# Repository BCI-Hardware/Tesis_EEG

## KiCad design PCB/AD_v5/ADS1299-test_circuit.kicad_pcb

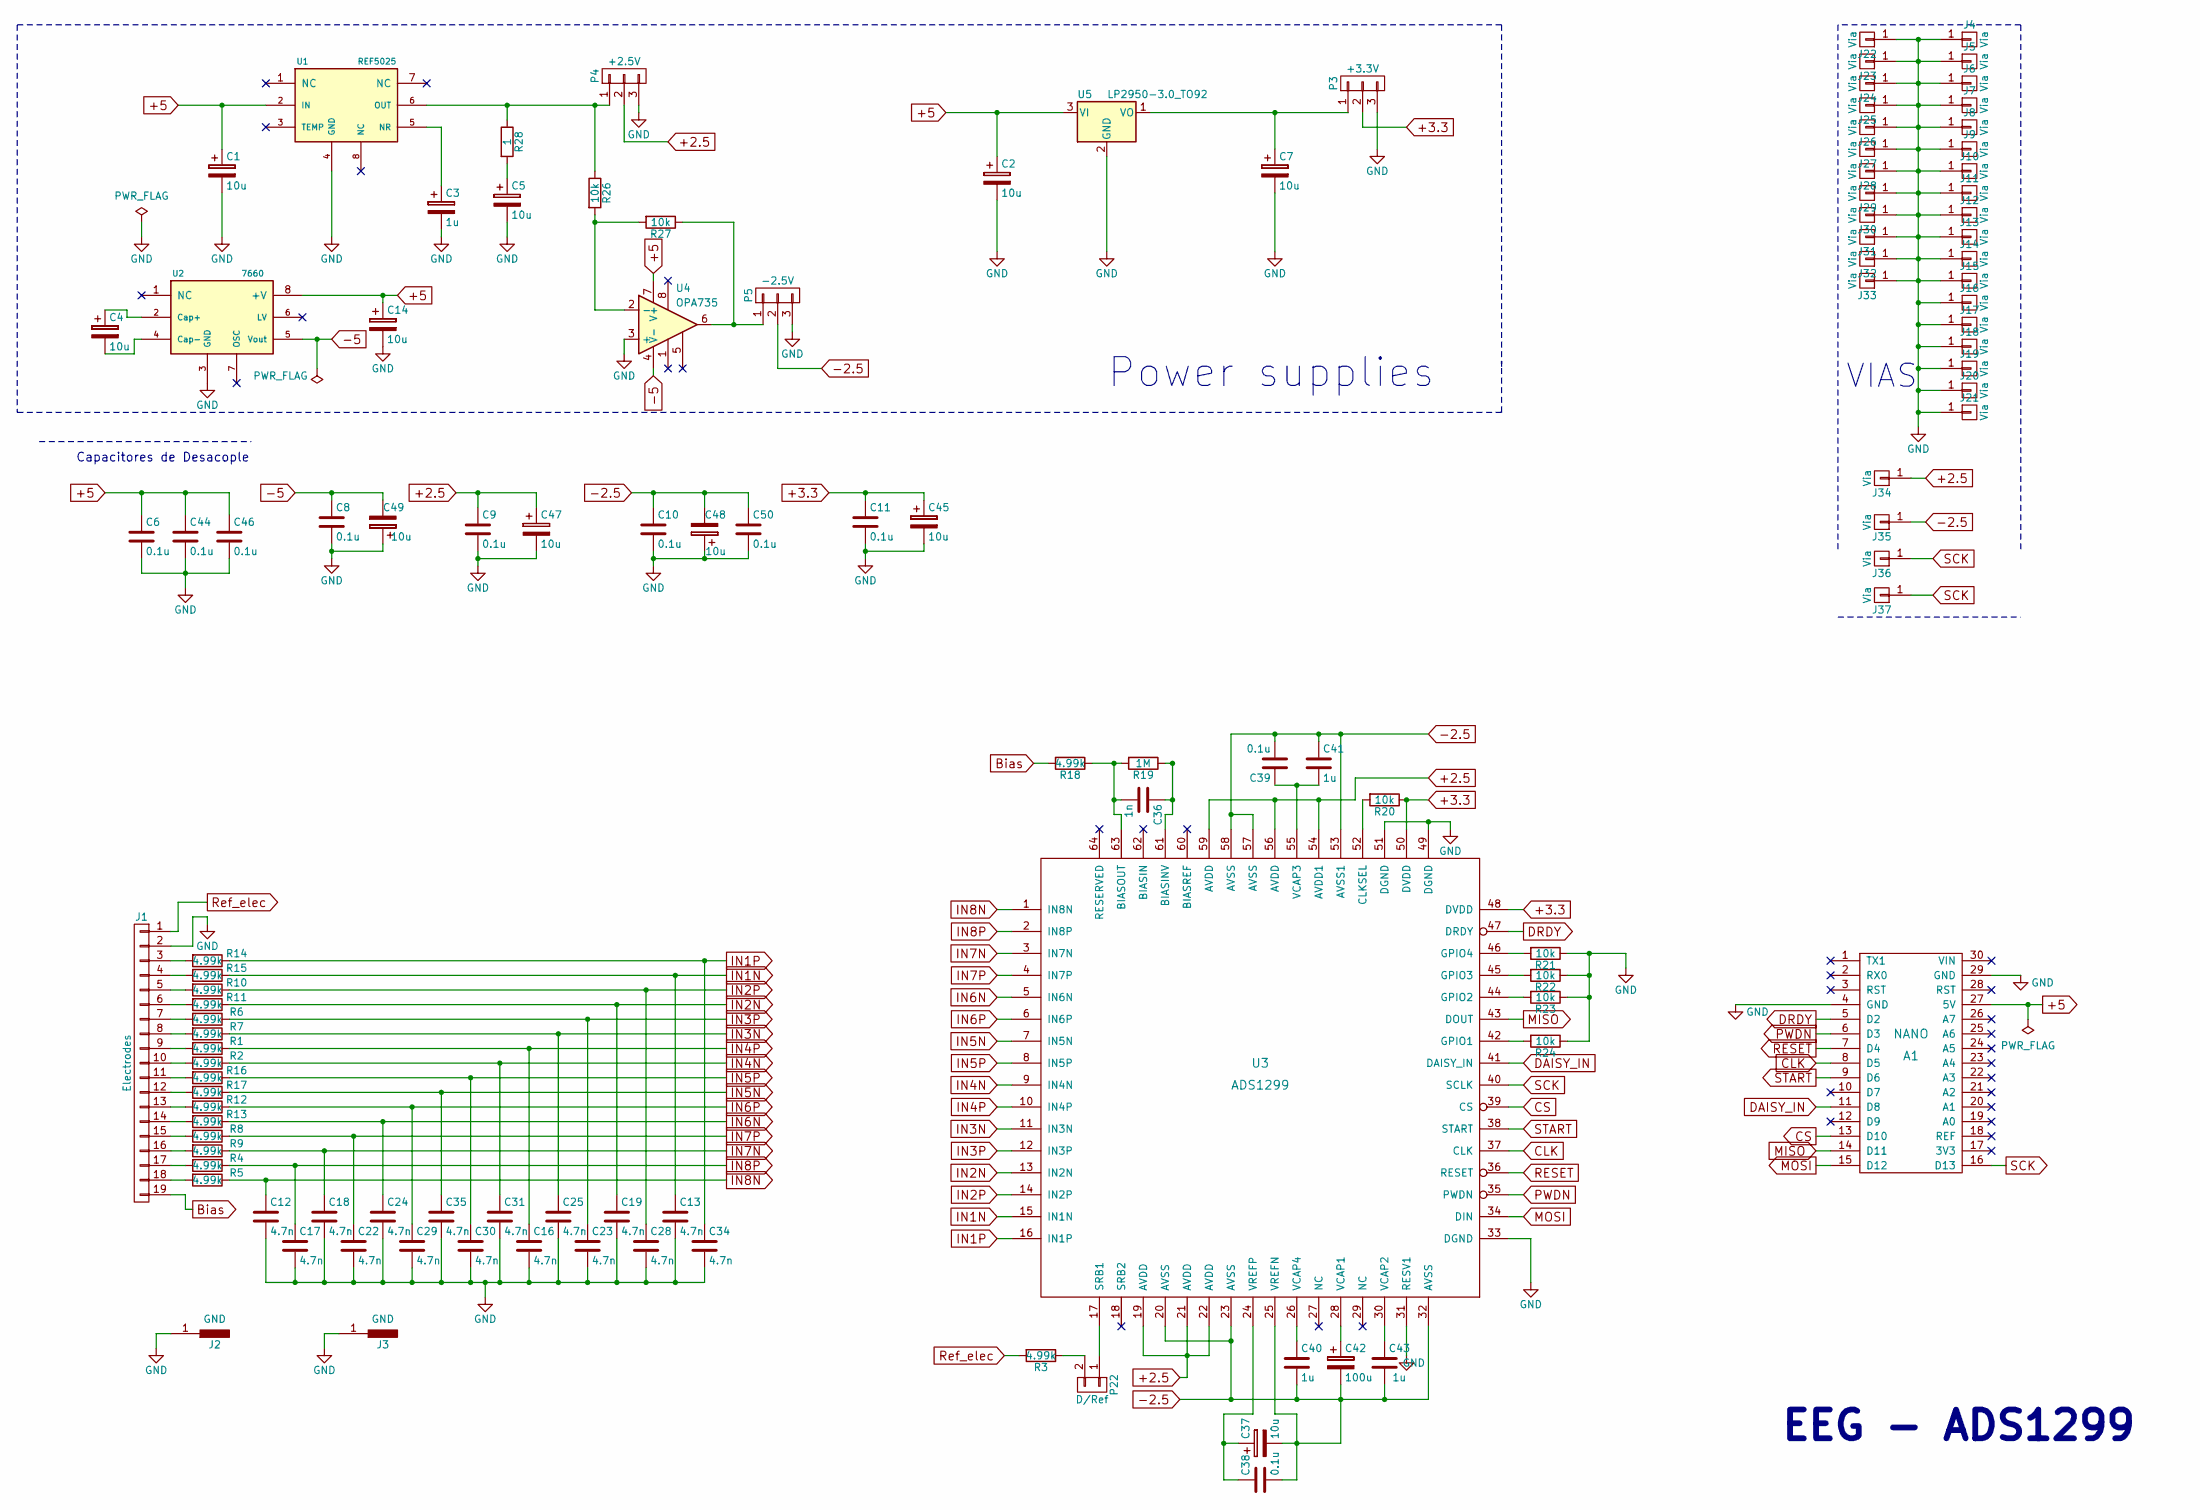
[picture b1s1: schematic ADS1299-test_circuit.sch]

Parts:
A1: NANO
C1, C2, C5, C7, C45, C47, C48, C49: 10u; CP_Elec_6.3x5.8
C3: 1u; CP_Elec_4x4.5
C4, C14: 10u; CP_Radial_D5.0mm_P2.50mm
C6, C8, C9, C10, C11, C38, C39, C44, C46, C50: 0.1u; C_0805
C12, C13, C16, C17, C18, C19, C22, C23, C24, C25, C28, C29, C30, C31, C34, C35: 4.7n; C_0805
C36: 1n; C_0805
C37: 10u; CP_Radial_Tantal_D5.0mm_P2.50mm
C40, C41, C43: 1u; C_0805
C42: 100u; CP_Radial_Tantal_D5.0mm_P2.50mm
J1: Electrodes; Pin_Header_Straight_1x19_Pitch2.54mm
J2, J3: GND; PINtorneado
J4, J5, J6, J7, J8, J9, J10, J11, J12, J13, J14, J15, J16, J17, J18, J19, J20, J21, J22, J23, J24, J25, J26, J27, J28, J29, J30, J31, J32, J33, J34, J35, J36, J37: Via; Pin_Header_Straight_1x01_Pitch2.54mm
P3: +3.3V; Pin_Header_Straight_1x03_Pitch2.54mm
P4: +2.5V; Pin_Header_Straight_1x03_Pitch2.54mm
P5: -2.5V; Pin_Header_Straight_1x03_Pitch2.54mm
P22: D/Ref; Pin_Header_Straight_1x02_Pitch2.54mm
R1, R2, R3, R4, R5, R6, R7, R8, R9, R10, R11, R12, R13, R14, R15, R16, R17, R18: 4.99k; R_0805
R19: 1M; R_0805
R20, R26, R27: 10k; R_0805
R21, R22, R23, R24: 10k; R_1206
R28: 1; R_0805
U1: REF5025; SOIC-8_3.9x4.9mm_Pitch1.27mm
U2: 7660; DIP-8_W7.62mm
U3: ADS1299; LQFP-64_10x10mm_Pitch0.5mm
U4: OPA735; SOIC-8_3.9x4.9mm_Pitch1.27mm
U5: LP2950-3.0_TO92; TO-92_Inline_Wide

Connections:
+2.5: C9.1, C47.1, J34.1, P4.2, U3.19 (AVDD), U3.21 (AVDD), U3.22 (AVDD), U3.54 (AVDD1), U3.56 (AVDD), U3.59 (AVDD)
+3.3: C11.1, C45.1, P3.2, R20.1, U3.48 (DVDD), U3.50 (DVDD)
+5: A1.27 (5V), C1.1, C2.1, C6.1, C14.1, C44.1, C46.1, U1.2 (IN), U2.8 (+V), U4.7 (V+), U5.3 (VI)
-2.5: C10.1, C37.2, C38.2, C39.2, C40.2, C41.1, C42.2, C43.2, C48.2, C50.1, J35.1, P5.2, U3.20 (AVSS), U3.23 (AVSS), U3.25 (VREFN), U3.32 (AVSS), U3.53 (AVSS1), U3.57 (AVSS), U3.58 (AVSS)
-5: C8.1, C49.2, U2.5 (Vout), U4.4 (V-)
Bias: J1.19, R18.2
CLK: A1.8 (D5), U3.37 (CLK)
CS: A1.13 (D10), U3.39 (CS)
DAISY_IN: A1.11 (D8), U3.41 (DAISY_IN)
DRDY: A1.5 (D2), U3.47 (DRDY)
GND: A1.4 (GND), A1.29 (GND), C1.2, C2.2, C3.2, C5.2, C6.2, C7.2, C8.2, C9.2, C10.2, C11.2, C12.2, C13.2, C14.2, C16.2, C17.2, C18.2, C19.2, C22.2, C23.2, C24.2, C25.2, C28.2, C29.2, C30.2, C31.2, C34.2, C35.2, C44.2, C45.2, C46.2, C47.2, C48.1, C49.1, C50.2, J1.2, J2.1, J3.1, J4.1, J5.1, J6.1, J7.1, J8.1, J9.1, J10.1, J11.1, J12.1, J13.1, J14.1, J15.1, J16.1, J17.1, J18.1, J19.1, J20.1, J21.1, J22.1, J23.1, J24.1, J25.1, J26.1, J27.1, J28.1, J29.1, J30.1, J31.1, J32.1, J33.1, P3.3, P4.3, P5.3, R21.1, R22.1, R23.1, R24.1, U1.4 (GND), U2.3 (GND), U3.31 (RESV1), U3.33 (DGND), U3.49 (DGND), U3.51 (DGND), U4.3 (+), U5.2 (GND)
IN1N: C13.1, R15.1, U3.15 (IN1N)
IN1P: C34.1, R14.1, U3.16 (IN1P)
IN2N: C19.1, R11.1, U3.13 (IN2N)
IN2P: C28.1, R10.1, U3.14 (IN2P)
IN3N: C25.1, R7.1, U3.11 (IN3N)
IN3P: C23.1, R6.1, U3.12 (IN3P)
IN4N: C31.1, R2.1, U3.9 (IN4N)
IN4P: C16.1, R1.1, U3.10 (IN4P)
IN5N: C35.1, R17.1, U3.7 (IN5N)
IN5P: C30.1, R16.1, U3.8 (IN5P)
IN6N: C24.1, R13.1, U3.5 (IN6N)
IN6P: C29.1, R12.1, U3.6 (IN6P)
IN7N: C18.1, R9.1, U3.3 (IN7N)
IN7P: C22.1, R8.1, U3.4 (IN7P)
IN8N: C12.1, R5.1, U3.1 (IN8N)
IN8P: C17.1, R4.1, U3.2 (IN8P)
MISO: A1.14 (D11), U3.43 (DOUT)
MOSI: A1.15 (D12), U3.34 (DIN)
unnamed: C3.1, U1.5 (NR)
unnamed: C4.1, U2.2 (Cap+)
unnamed: C4.2, U2.4 (Cap-)
unnamed: C5.1, R28.2
unnamed: C7.1, P3.1, U5.1 (VO)
unnamed: C36.1, R19.1, U3.61 (BIASINV)
unnamed: C36.2, R18.1, R19.2, U3.63 (BIASOUT)
unnamed: C37.1, C38.1, U3.24 (VREFP)
unnamed: C39.1, C41.2, U3.55 (VCAP3)
unnamed: C40.1, U3.26 (VCAP4)
unnamed: C42.1, U3.28 (VCAP1)
unnamed: C43.1, U3.30 (VCAP2)
unnamed: J1.3, R14.2
unnamed: J1.4, R15.2
unnamed: J1.5, R10.2
unnamed: J1.6, R11.2
unnamed: J1.7, R6.2
unnamed: J1.8, R7.2
unnamed: J1.9, R1.2
unnamed: J1.10, R2.2
unnamed: J1.11, R16.2
unnamed: J1.12, R17.2
unnamed: J1.13, R12.2
unnamed: J1.14, R13.2
unnamed: J1.15, R8.2
unnamed: J1.16, R9.2
unnamed: J1.17, R4.2
unnamed: J1.18, R5.2
unnamed: P4.1, R26.1, R28.1, U1.6 (OUT)
unnamed: P5.1, R27.1, U4.6
unnamed: P22.1, U3.17 (SRB1)
unnamed: P22.2, R3.1
unnamed: R20.2, U3.52 (CLKSEL)
unnamed: R21.2, U3.46 (GPIO4)
unnamed: R22.2, U3.45 (GPIO3)
unnamed: R23.2, U3.44 (GPIO2)
unnamed: R24.2, U3.42 (GPIO1)
unnamed: R26.2, R27.2, U4.2 (-)
PWDN: A1.6 (D3), U3.35 (PWDN)
RESET: A1.7 (D4), U3.36 (RESET)
Ref_elec: J1.1, R3.2
SCK: A1.16 (D13), J36.1, J37.1, U3.40 (SCLK)
START: A1.9 (D6), U3.38 (START)

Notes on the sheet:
Power supplies
Capacitores de Desacople
EEG - ADS1299
VIAS

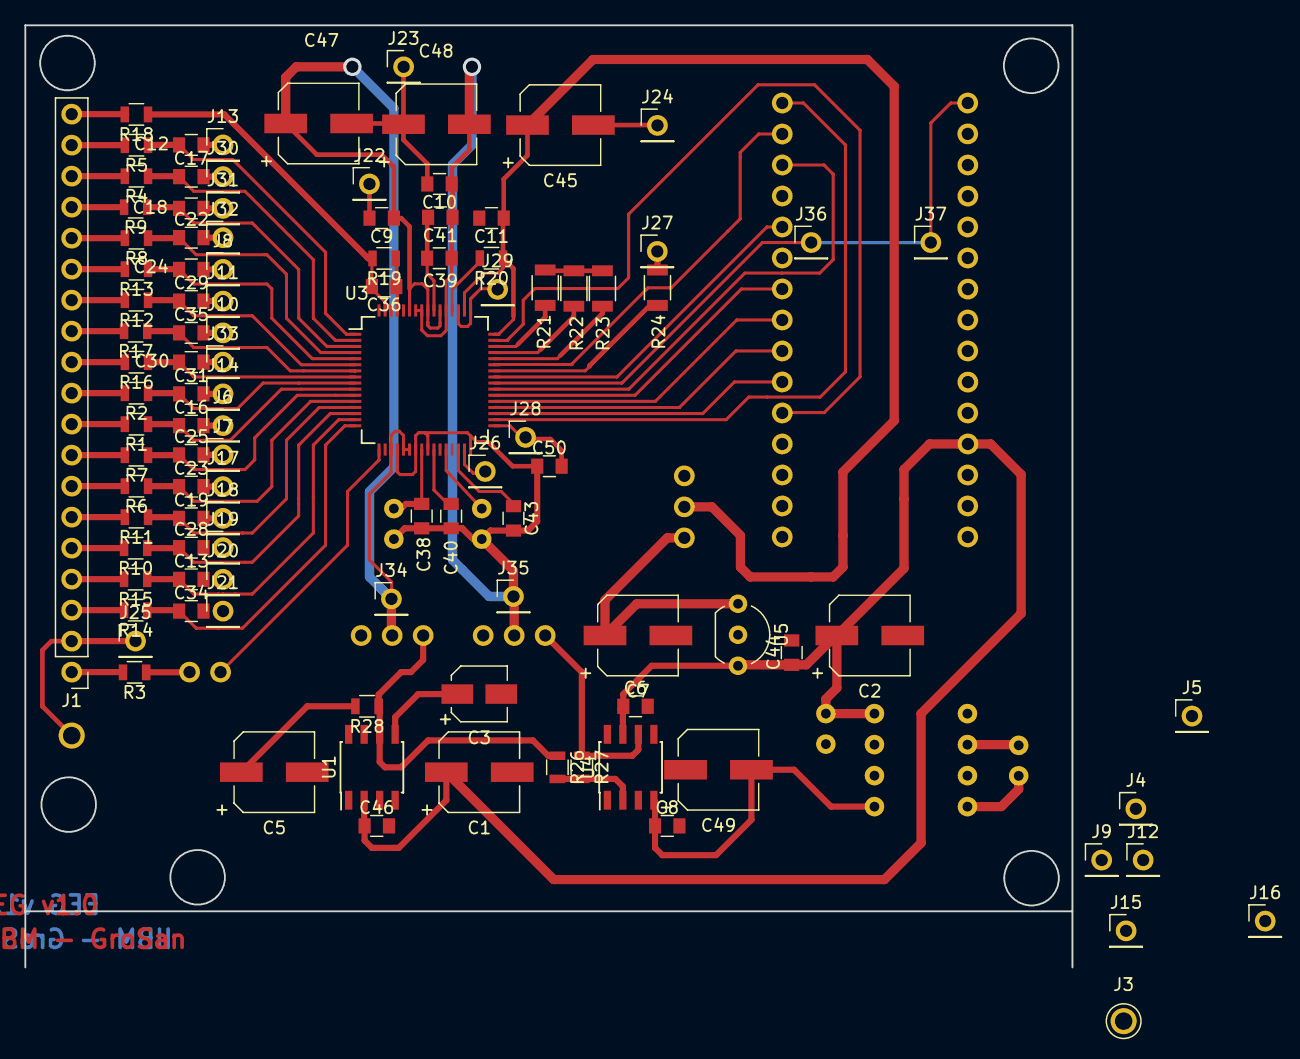
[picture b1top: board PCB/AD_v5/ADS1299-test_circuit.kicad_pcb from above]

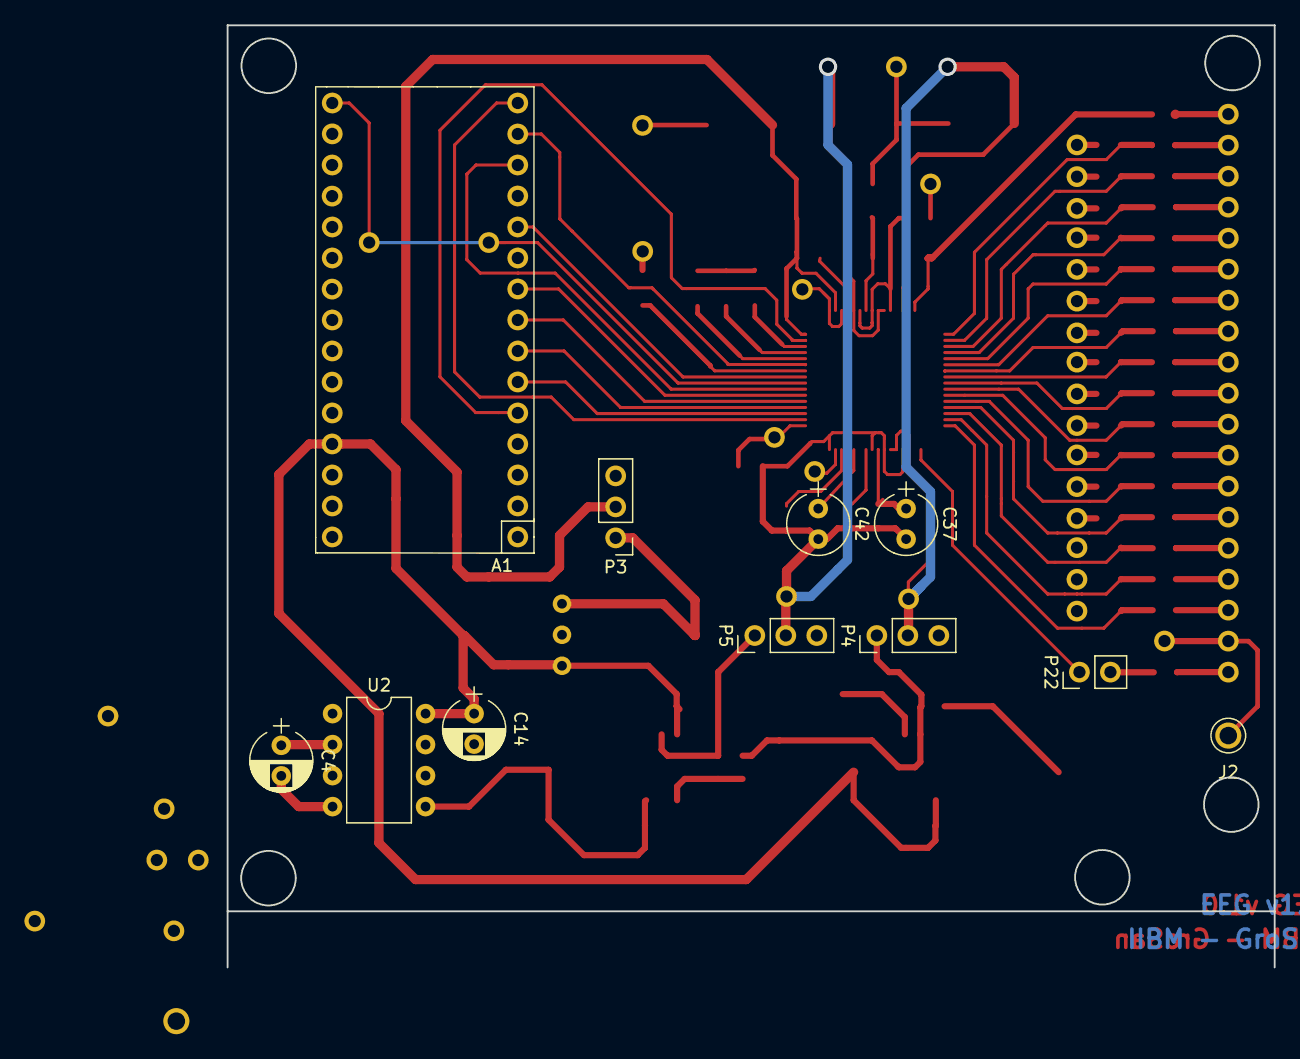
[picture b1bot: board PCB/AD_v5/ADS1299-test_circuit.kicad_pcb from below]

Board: 2 copper layers, 85.8 x 77.2 mm, 117 parts (11 on the bottom side), 72 nets.

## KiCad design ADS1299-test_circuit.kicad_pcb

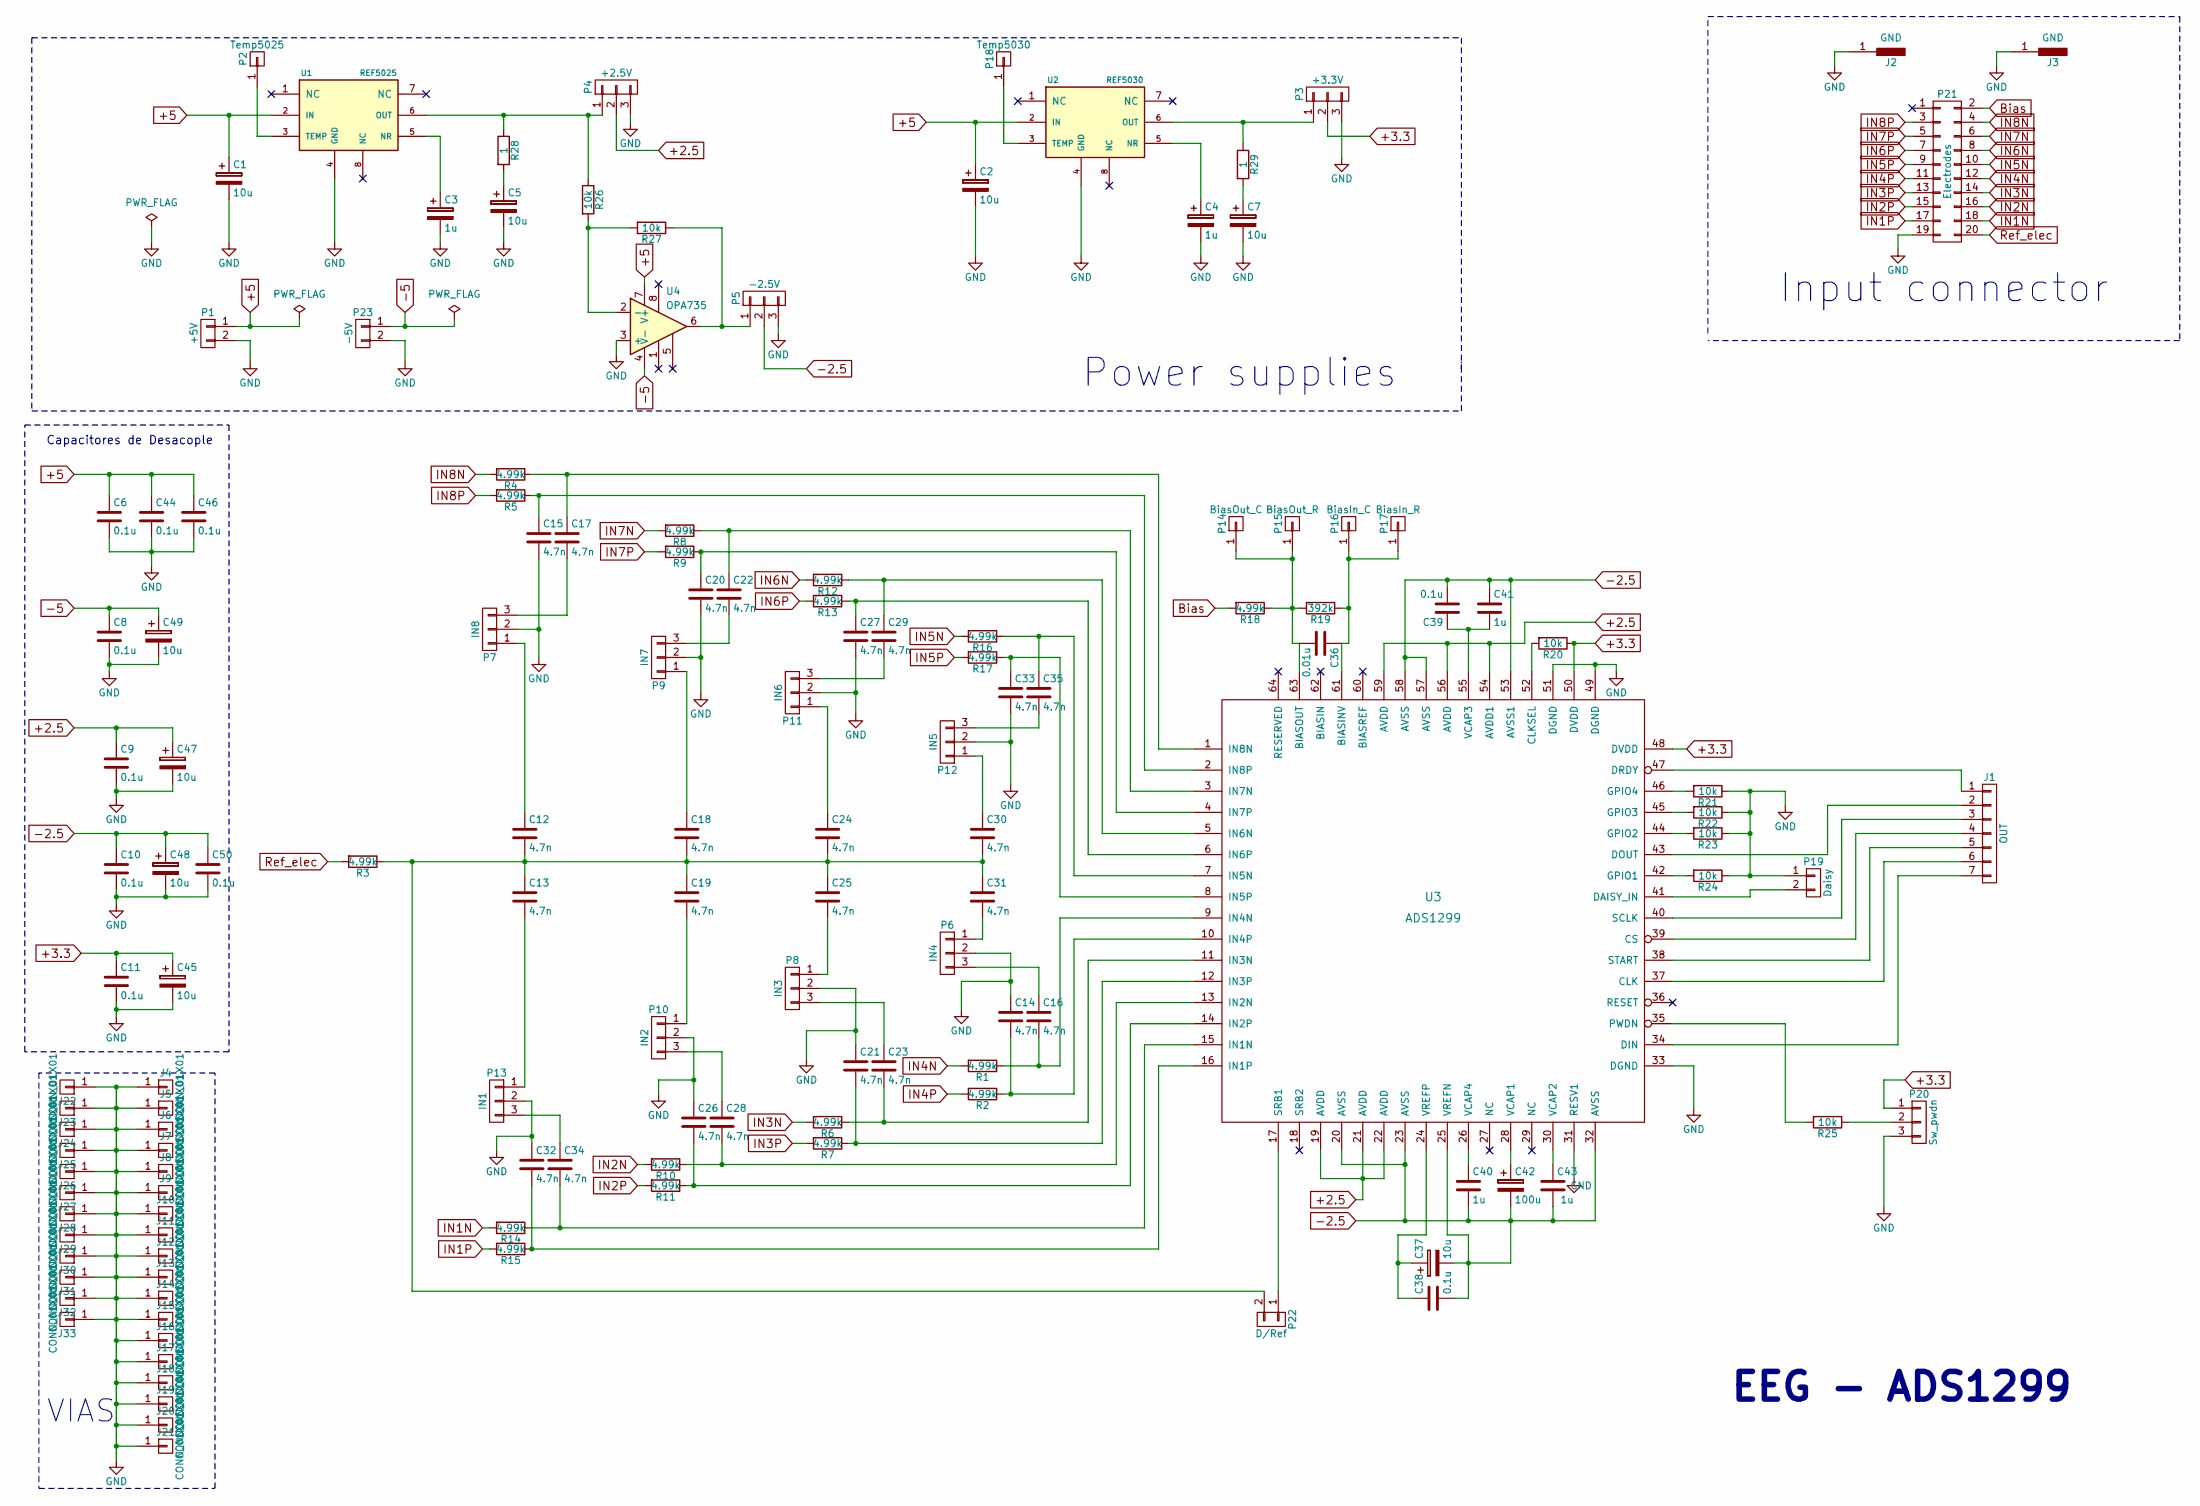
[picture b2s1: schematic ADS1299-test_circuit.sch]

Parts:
C1, C2, C5, C7, C45, C47, C48, C49: 10u; CP_Elec_6.3x5.8
C3, C4: 1u; CP_Elec_4x4.5
C6, C8, C9, C10, C11, C38, C39, C44, C46, C50: 0.1u; C_0805
C12, C13, C18, C19, C24, C25, C30, C31: 4.7n; C_0805
C14, C15, C16, C17, C20, C21, C22, C23, C26, C27, C28, C29, C32, C33, C34, C35: 4.7n; C_1206
C36: 0.01u; C_0805
C37: 10u; CP_Radial_Tantal_D5.0mm_P2.50mm
C40, C41, C43: 1u; C_0805
C42: 100u; CP_Radial_Tantal_D5.0mm_P2.50mm
J1: OUT; Pin_Header_Straight_1x07_Pitch2.54mm
J2, J3: GND; PINtorneado
J4, J5, J6, J7, J8, J9, J10, J11, J12, J13, J14, J15, J16, J17, J18, J19, J20, J21, J22, J23, J24, J25, J26, J27, J28, J29, J30, J31, J32, J33: CONN_01X01; Pin_Header_Straight_1x01_Pitch2.54mm
P1: +5V; Pin_Header_Straight_1x02_Pitch2.54mm
P2: Temp5025; Pin_Header_Straight_1x01_Pitch2.54mm
P3: +3.3V; Pin_Header_Straight_1x03_Pitch2.54mm
P4: +2.5V; Pin_Header_Straight_1x03_Pitch2.54mm
P5: -2.5V; Pin_Header_Straight_1x03_Pitch2.54mm
P6: IN4; Pin_Header_Straight_1x03_Pitch2.54mm
P7: IN8; Pin_Header_Straight_1x03_Pitch2.54mm
P8: IN3; Pin_Header_Straight_1x03_Pitch2.54mm
P9: IN7; Pin_Header_Straight_1x03_Pitch2.54mm
P10: IN2; Pin_Header_Straight_1x03_Pitch2.54mm
P11: IN6; Pin_Header_Straight_1x03_Pitch2.54mm
P12: IN5; Pin_Header_Straight_1x03_Pitch2.54mm
P13: IN1; Pin_Header_Straight_1x03_Pitch2.54mm
P14: BiasOut_C; Pin_Header_Straight_1x01_Pitch2.54mm
P15: BiasOut_R; Pin_Header_Straight_1x01_Pitch2.54mm
P16: BiasIn_C; Pin_Header_Straight_1x01_Pitch2.54mm
P17: BiasIn_R; Pin_Header_Straight_1x01_Pitch2.54mm
P18: Temp5030; Pin_Header_Straight_1x01_Pitch2.54mm
P19: Daisy; Pin_Header_Straight_1x02_Pitch2.54mm
P20: Sw_pwdn; Pin_Header_Straight_1x03_Pitch2.54mm
P21: Electrodes; Pin_Header_Straight_2x10_Pitch2.54mm
P22: D/Ref; Pin_Header_Straight_1x02_Pitch2.54mm
P23: -5V; Pin_Header_Straight_1x02_Pitch2.54mm
R1, R2, R3, R4, R5, R6, R7, R8, R9, R10, R11, R12, R13, R14, R15, R16, R17, R18: 4.99k; R_0805
R19: 392k; R_0805
R20, R26, R27: 10k; R_0805
R21, R22, R23, R24, R25: 10k; R_1206
R28, R29: 1; R_0805
U1: REF5025; SOIC-8_3.9x4.9mm_Pitch1.27mm
U2: REF5030; SOIC-8_3.9x4.9mm_Pitch1.27mm
U3: ADS1299; LQFP-64_10x10mm_Pitch0.5mm
U4: OPA735; SOIC-8_3.9x4.9mm_Pitch1.27mm

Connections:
+2.5: C9.1, C47.1, P4.2, U3.19 (AVDD), U3.21 (AVDD), U3.22 (AVDD), U3.54 (AVDD1), U3.56 (AVDD), U3.59 (AVDD)
+3.3: C11.1, C45.1, P3.2, P20.1, R20.1, U3.48 (DVDD), U3.50 (DVDD)
+5: C1.1, C2.1, C6.1, C44.1, C46.1, P1.1, U1.2 (IN), U2.2 (IN), U4.7 (V+)
-2.5: C10.1, C37.2, C38.2, C39.2, C40.2, C41.1, C42.2, C43.2, C48.1, C50.1, P5.2, U3.20 (AVSS), U3.23 (AVSS), U3.25 (VREFN), U3.32 (AVSS), U3.53 (AVSS1), U3.57 (AVSS), U3.58 (AVSS)
-5: C8.1, C49.1, P23.1, U4.4 (V-)
Bias: P21.2, R18.2
GND: C1.2, C2.2, C3.2, C4.2, C5.2, C6.2, C7.2, C8.2, C9.2, C10.2, C11.2, C14.1, C15.2, C20.2, C21.1, C26.1, C27.2, C32.1, C33.2, C44.2, C45.2, C46.2, C47.2, C48.2, C49.2, C50.2, J2.1, J3.1, J4.1, J5.1, J6.1, J7.1, J8.1, J9.1, J10.1, J11.1, J12.1, J13.1, J14.1, J15.1, J16.1, J17.1, J18.1, J19.1, J20.1, J21.1, J22.1, J23.1, J24.1, J25.1, J26.1, J27.1, J28.1, J29.1, J30.1, J31.1, J32.1, J33.1, P1.2, P3.3, P4.3, P5.3, P6.2, P7.2, P8.2, P9.2, P10.2, P11.2, P12.2, P13.2, P19.1, P20.3, P21.19, P23.2, R21.1, R22.1, R23.1, R24.1, U1.4 (GND), U2.4 (GND), U3.31 (RESV1), U3.33 (DGND), U3.49 (DGND), U3.51 (DGND), U4.3 (+)
IN1N: P21.18, R14.2
IN1P: P21.17, R15.2
IN2N: P21.16, R10.2
IN2P: P21.15, R11.2
IN3N: P21.14, R6.2
IN3P: P21.13, R7.2
IN4N: P21.12, R1.2
IN4P: P21.11, R2.2
IN5N: P21.10, R16.2
IN5P: P21.9, R17.2
IN6N: P21.8, R12.2
IN6P: P21.7, R13.2
IN7N: P21.6, R8.2
IN7P: P21.5, R9.2
IN8N: P21.4, R4.2
IN8P: P21.3, R5.2
unnamed: C3.1, U1.5 (NR)
unnamed: C4.1, U2.5 (NR)
unnamed: C5.1, R28.2
unnamed: C7.1, R29.2
unnamed: C12.1, P7.1
unnamed: C12.2, C13.1, C18.2, C19.1, C24.2, C25.1, C30.2, C31.1, P22.2, R3.1
unnamed: C13.2, P13.1
unnamed: C14.2, R2.1, U3.10 (IN4P)
unnamed: C15.1, R5.1, U3.2 (IN8P)
unnamed: C16.1, P6.3
unnamed: C16.2, R1.1, U3.9 (IN4N)
unnamed: C17.1, R4.1, U3.1 (IN8N)
unnamed: C17.2, P7.3
unnamed: C18.1, P9.1
unnamed: C19.2, P10.1
unnamed: C20.1, R9.1, U3.4 (IN7P)
unnamed: C21.2, R7.1, U3.12 (IN3P)
unnamed: C22.1, R8.1, U3.3 (IN7N)
unnamed: C22.2, P9.3
unnamed: C23.1, P8.3
unnamed: C23.2, R6.1, U3.11 (IN3N)
unnamed: C24.1, P11.1
unnamed: C25.2, P8.1
unnamed: C26.2, R11.1, U3.14 (IN2P)
unnamed: C27.1, R13.1, U3.6 (IN6P)
unnamed: C28.1, P10.3
unnamed: C28.2, R10.1, U3.13 (IN2N)
unnamed: C29.1, R12.1, U3.5 (IN6N)
unnamed: C29.2, P11.3
unnamed: C30.1, P12.1
unnamed: C31.2, P6.1
unnamed: C32.2, R15.1, U3.16 (IN1P)
unnamed: C33.1, R17.1, U3.8 (IN5P)
unnamed: C34.1, P13.3
unnamed: C34.2, R14.1, U3.15 (IN1N)
unnamed: C35.1, R16.1, U3.7 (IN5N)
unnamed: C35.2, P12.3
unnamed: C36.1, P16.1, P17.1, R19.1, U3.61 (BIASINV)
unnamed: C36.2, P14.1, P15.1, R18.1, R19.2, U3.63 (BIASOUT)
unnamed: C37.1, C38.1, U3.24 (VREFP)
unnamed: C39.1, C41.2, U3.55 (VCAP3)
unnamed: C40.1, U3.26 (VCAP4)
unnamed: C42.1, U3.28 (VCAP1)
unnamed: C43.1, U3.30 (VCAP2)
unnamed: J1.1, U3.47 (DRDY)
unnamed: J1.2, U3.43 (DOUT)
unnamed: J1.3, U3.40 (SCLK)
unnamed: J1.4, U3.39 (CS)
unnamed: J1.5, U3.38 (START)
unnamed: J1.6, U3.37 (CLK)
unnamed: J1.7, U3.34 (DIN)
unnamed: P2.1, U1.3 (TEMP)
unnamed: P3.1, R29.1, U2.6 (OUT)
unnamed: P4.1, R26.1, R28.1, U1.6 (OUT)
unnamed: P5.1, R27.1, U4.6
unnamed: P18.1, U2.3 (TEMP)
unnamed: P19.2, U3.41 (DAISY_IN)
unnamed: P20.2, R25.1
unnamed: P22.1, U3.17 (SRB1)
unnamed: R20.2, U3.52 (CLKSEL)
unnamed: R21.2, U3.46 (GPIO4)
unnamed: R22.2, U3.45 (GPIO3)
unnamed: R23.2, U3.44 (GPIO2)
unnamed: R24.2, U3.42 (GPIO1)
unnamed: R25.2, U3.35 (PWDN)
unnamed: R26.2, R27.2, U4.2 (-)
Ref_elec: P21.20, R3.2

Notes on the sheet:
Power supplies
Input connector
Capacitores de Desacople
EEG - ADS1299
VIAS

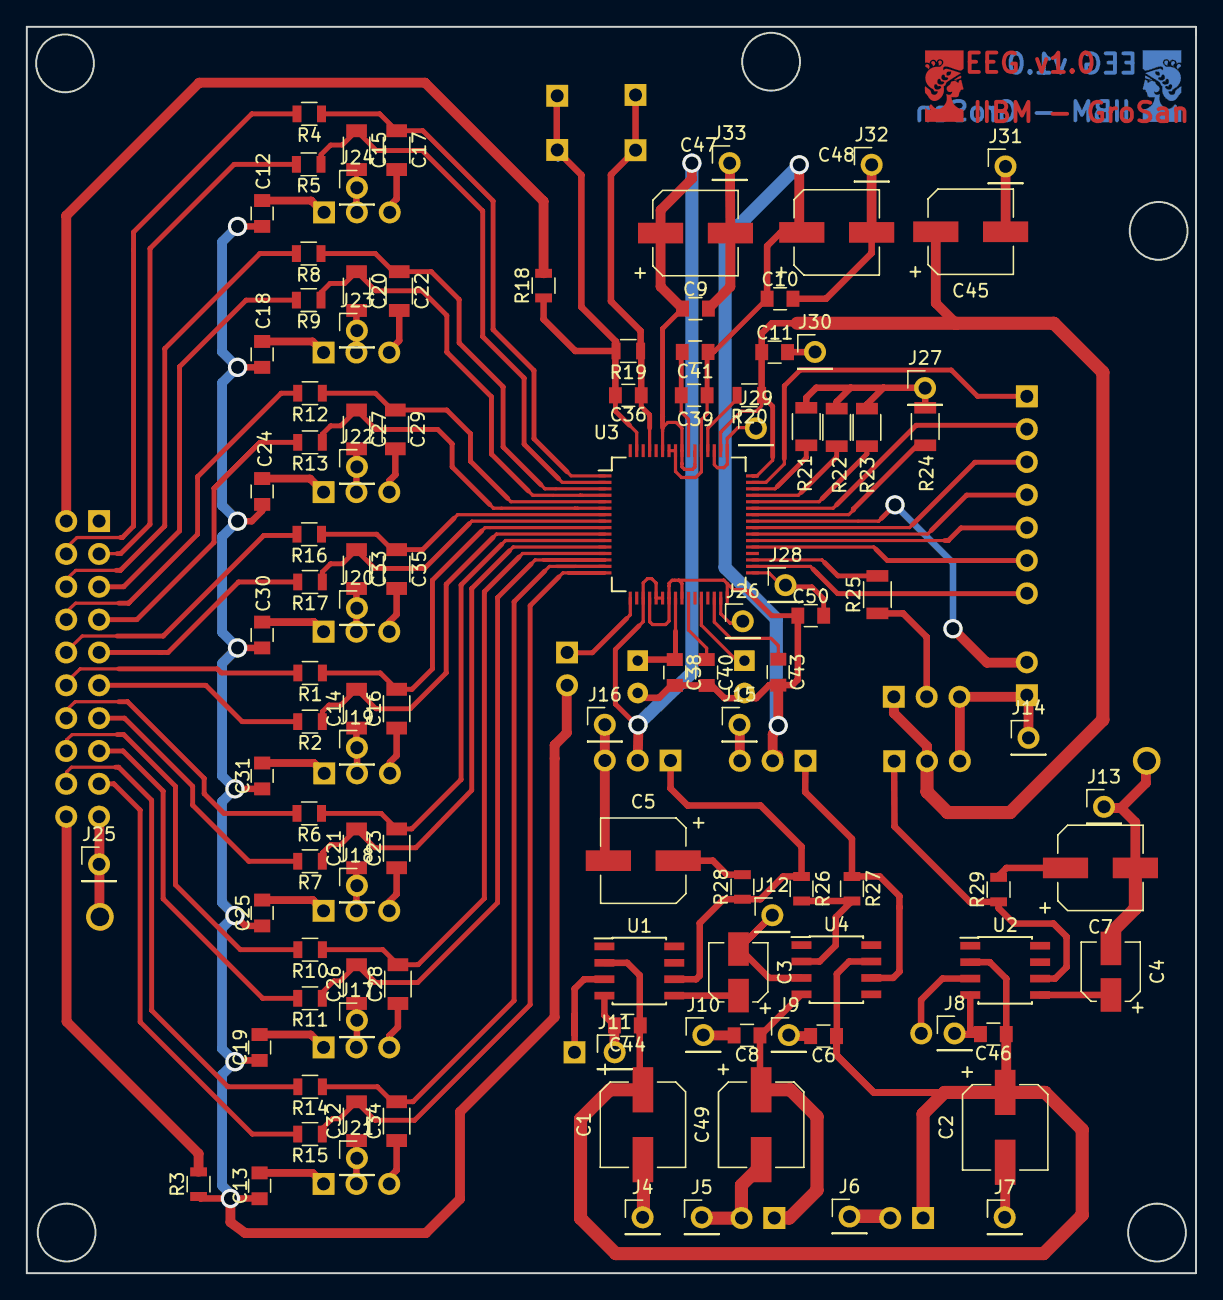
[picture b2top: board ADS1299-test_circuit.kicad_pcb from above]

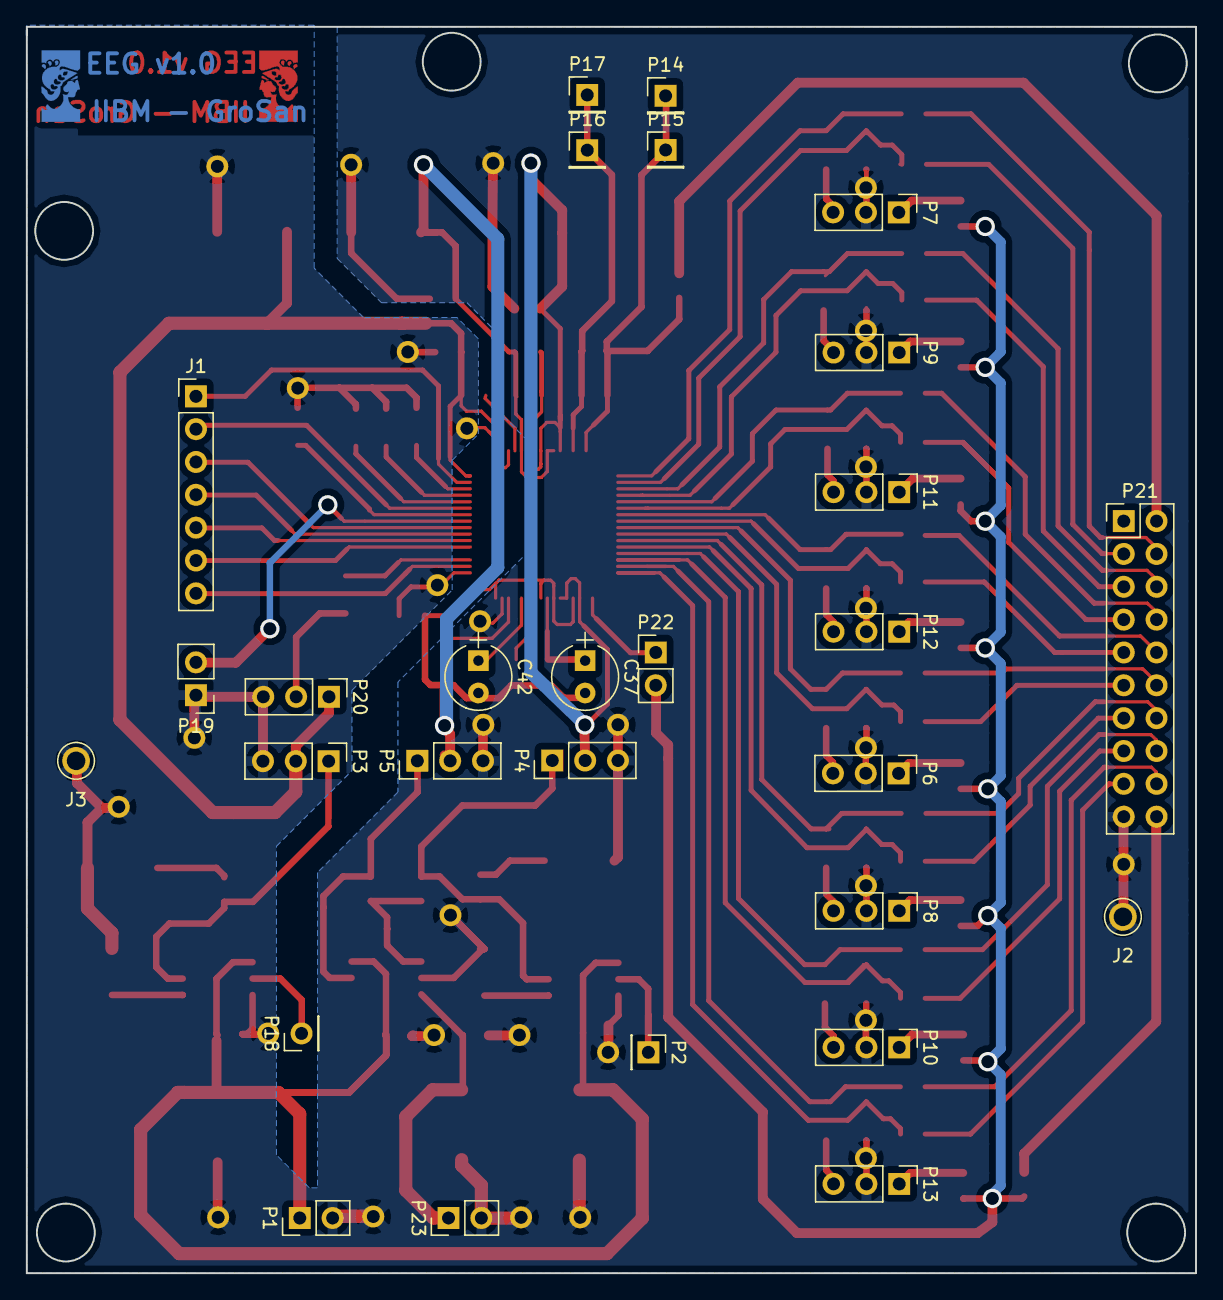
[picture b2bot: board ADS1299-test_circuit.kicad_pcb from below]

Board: 2 copper layers, 90.4 x 96.4 mm, 139 parts (28 on the bottom side), 90 nets.

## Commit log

2017-04-17 PCB del prototipo con 8 electrodos - v1.0 - Falta agregar pines de prueba
2017-04-17 Hojas de datos y notas de aplicación para el diseño de EEGs
2017-04-17 Agrego lista de pendientes
2017-05-02 Agrego circuito revisado por Brian y lista de componentes. Falta comprar los capacitores para completar el circuito
2017-05-21 Circuito modificado de acuerdo al tamanio de los capacitores. Tira de pines invertidas
2017-05-21 Agrego diagrama en bloques de conexionado de la placa
2017-07-09 Brian: ajustes del pcb. V1.0
2017-07-10 Agrego pines torneados para GND, logo fiuba y acomodo pistas
2017-07-11 Correccion de pines, masa, capacitores.
2017-07-13 Arreglos LCI
    - Pistas mas gruesas donde es posible.
    - Pines de TEMP se corrigieron a 2.57mm.
2017-07-14 Correcciones LCI
    Ahora las vias son pines con thermal relief.
2018-04-03 Update Arduino and matlab code
2018-04-03 Move PCB files
2018-04-17 split data processing functions
2019-08-22 Update repo
2019-09-27 Add live processing
